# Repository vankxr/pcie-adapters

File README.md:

# pcie-adapters
Collection of PCI Express adapter hardware

## Authors

* **João Silva** - [vankxr](https://github.com/vankxr)

## License

The content of this repository is licensed under the [GNU General Public License v3.0](LICENSE).

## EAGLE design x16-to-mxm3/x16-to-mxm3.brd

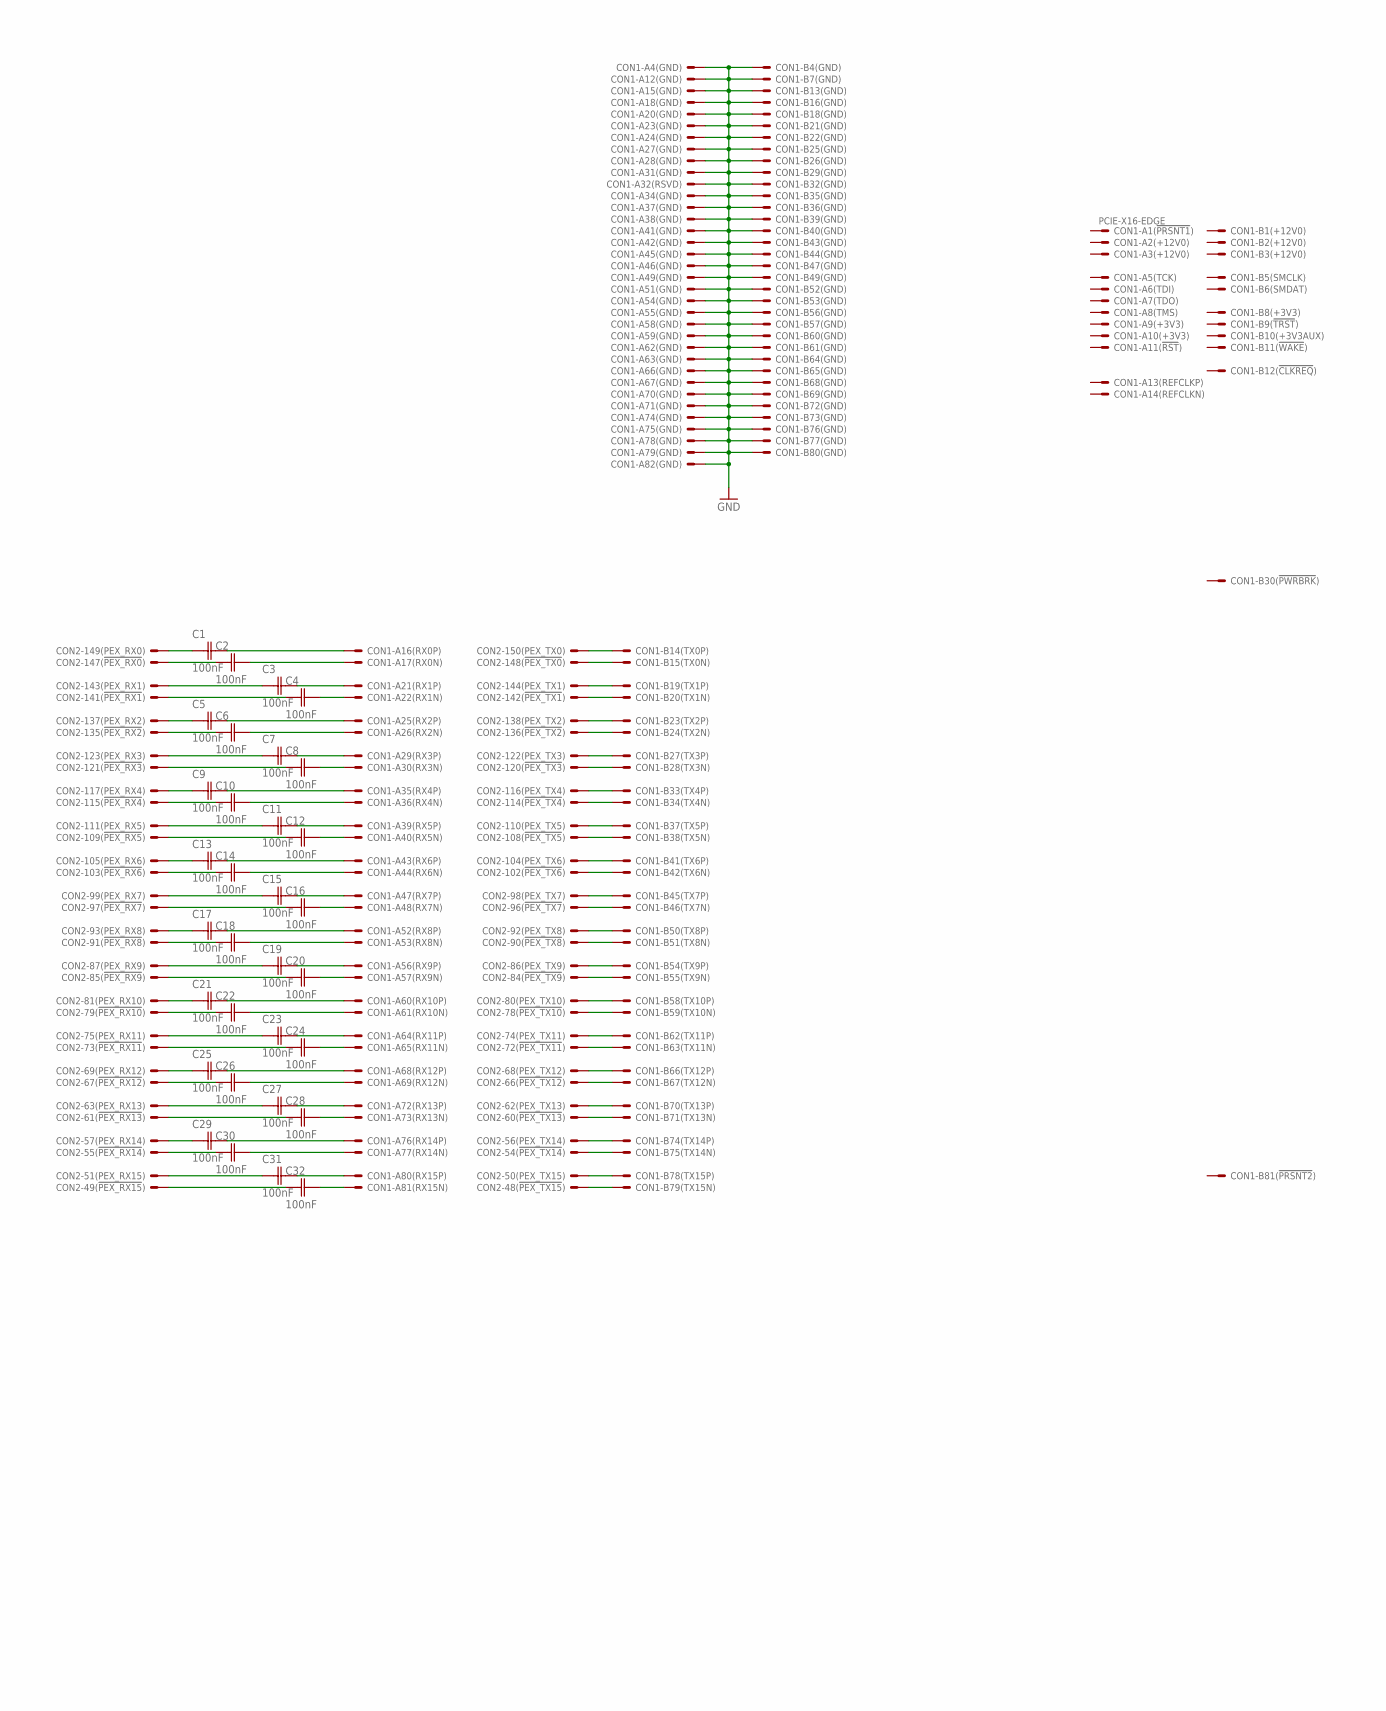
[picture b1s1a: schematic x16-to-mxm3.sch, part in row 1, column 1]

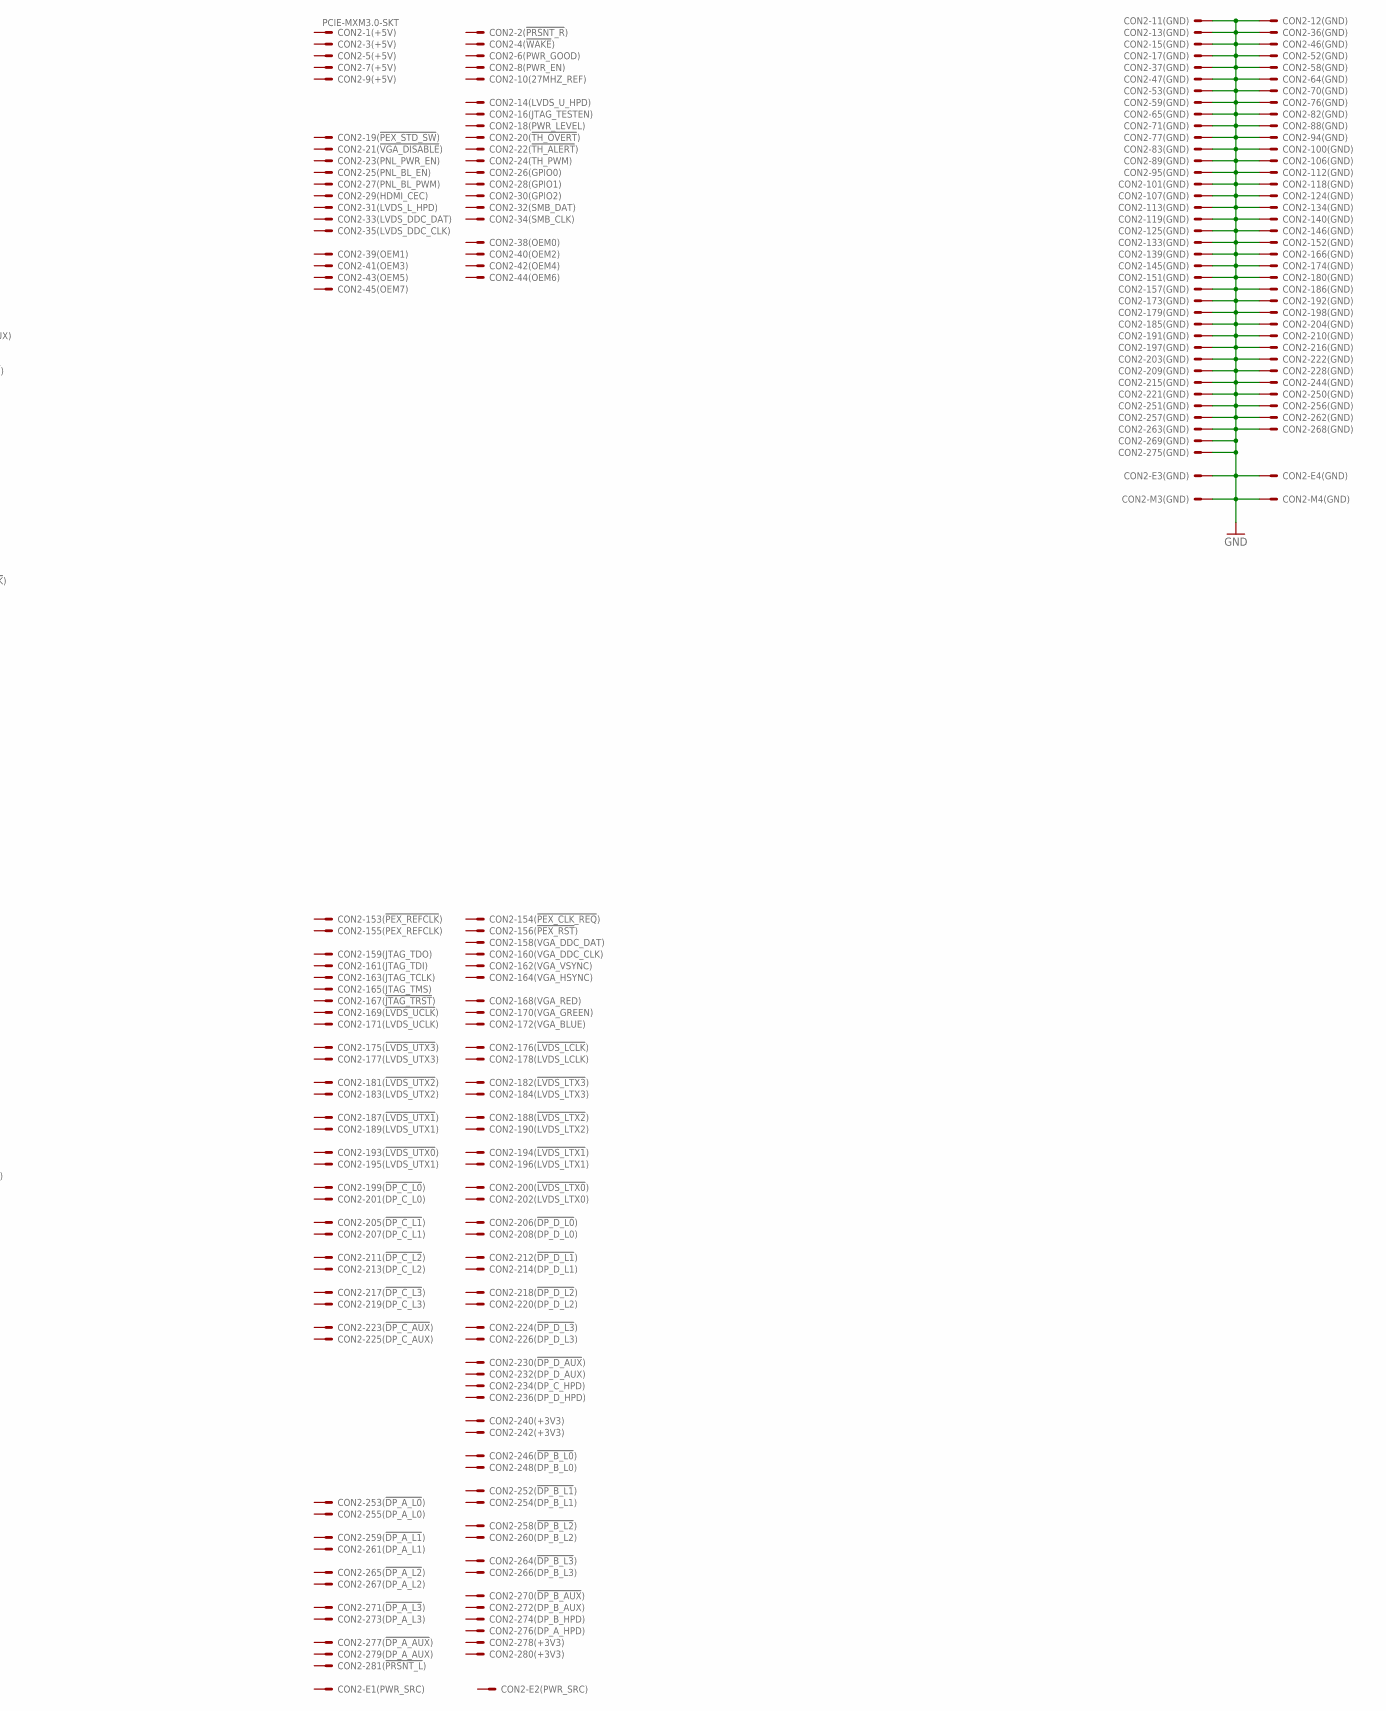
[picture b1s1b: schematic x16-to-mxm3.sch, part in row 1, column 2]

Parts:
C1, C2, C3, C4, C5, C6, C7, C8, C9, C10, C11, C12, C13, C14, C15, C16, C17, C18, C19, C20, C21, C22, C23, C24, C25, C26, C27, C28, C29, C30, C31, C32: 100nF; CAP0402
CON1: PCIE-X16-EDGE
CON2: PCIE-MXM3.0-SKT

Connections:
GND: CON1.A4, CON1.A12, CON1.A15, CON1.A18, CON1.A20, CON1.A23, CON1.A24, CON1.A27, CON1.A28, CON1.A31, CON1.A32, CON1.A34, CON1.A37, CON1.A38, CON1.A41, CON1.A42, CON1.A45, CON1.A46, CON1.A49, CON1.A51, CON1.A54, CON1.A55, CON1.A58, CON1.A59, CON1.A62, CON1.A63, CON1.A66, CON1.A67, CON1.A70, CON1.A71, CON1.A74, CON1.A75, CON1.A78, CON1.A79, CON1.A82, CON1.B4, CON1.B7, CON1.B13, CON1.B16, CON1.B18, CON1.B21, CON1.B22, CON1.B25, CON1.B26, CON1.B29, CON1.B32, CON1.B35, CON1.B36, CON1.B39, CON1.B40, CON1.B43, CON1.B44, CON1.B47, CON1.B49, CON1.B52, CON1.B53, CON1.B56, CON1.B57, CON1.B60, CON1.B61, CON1.B64, CON1.B65, CON1.B68, CON1.B69, CON1.B72, CON1.B73, CON1.B76, CON1.B77, CON1.B80, CON2.11, CON2.12, CON2.13, CON2.15, CON2.17, CON2.36, CON2.37, CON2.46, CON2.47, CON2.52, CON2.53, CON2.58, CON2.59, CON2.64, CON2.65, CON2.70, CON2.71, CON2.76, CON2.77, CON2.82, CON2.83, CON2.88, CON2.89, CON2.94, CON2.95, CON2.100, CON2.101, CON2.106, CON2.107, CON2.112, CON2.113, CON2.118, CON2.119, CON2.124, CON2.125, CON2.133, CON2.134, CON2.139, CON2.140, CON2.145, CON2.146, CON2.151, CON2.152, CON2.157, CON2.166, CON2.173, CON2.174, CON2.179, CON2.180, CON2.185, CON2.186, CON2.191, CON2.192, CON2.197, CON2.198, CON2.203, CON2.204, CON2.209, CON2.210, CON2.215, CON2.216, CON2.221, CON2.222, CON2.228, CON2.244, CON2.250, CON2.251, CON2.256, CON2.257, CON2.262, CON2.263, CON2.268, CON2.269, CON2.275, CON2.E3, CON2.E4, CON2.M3, CON2.M4
unnamed: CON1.B14, CON2.150
unnamed: CON1.B15, CON2.148
unnamed: CON1.B19, CON2.144
unnamed: CON1.B20, CON2.142
unnamed: CON1.B23, CON2.138
unnamed: CON1.B24, CON2.136
unnamed: CON1.B27, CON2.122
unnamed: CON1.B28, CON2.120
unnamed: CON1.B33, CON2.116
unnamed: CON1.B34, CON2.114
unnamed: CON1.B37, CON2.110
unnamed: CON1.B38, CON2.108
unnamed: CON1.B41, CON2.104
unnamed: CON1.B42, CON2.102
unnamed: CON1.B45, CON2.98
unnamed: CON1.B46, CON2.96
unnamed: CON1.B50, CON2.92
unnamed: CON1.B51, CON2.90
unnamed: CON1.B54, CON2.86
unnamed: CON1.B55, CON2.84
unnamed: CON1.B58, CON2.80
unnamed: CON1.B59, CON2.78
unnamed: CON1.B62, CON2.74
unnamed: CON1.B63, CON2.72
unnamed: CON1.B66, CON2.68
unnamed: CON1.B67, CON2.66
unnamed: CON1.B70, CON2.62
unnamed: CON1.B71, CON2.60
unnamed: CON1.B74, CON2.56
unnamed: CON1.B75, CON2.54
unnamed: CON1.B78, CON2.50
unnamed: CON1.B79, CON2.48
unnamed: C4.2 (C2), CON1.A22
unnamed: C8.2 (C2), CON1.A30
unnamed: C12.2 (C2), CON1.A40
unnamed: C16.2 (C2), CON1.A48
unnamed: C20.2 (C2), CON1.A57
unnamed: C24.2 (C2), CON1.A65
unnamed: C28.2 (C2), CON1.A73
unnamed: C32.2 (C2), CON1.A81
unnamed: C2.2 (C2), CON1.A17
unnamed: C6.2 (C2), CON1.A26
unnamed: C10.2 (C2), CON1.A36
unnamed: C14.2 (C2), CON1.A44
unnamed: C18.2 (C2), CON1.A53
unnamed: C22.2 (C2), CON1.A61
unnamed: C26.2 (C2), CON1.A69
unnamed: C30.2 (C2), CON1.A77
unnamed: C1.2 (C2), CON1.A16
unnamed: C5.2 (C2), CON1.A25
unnamed: C9.2 (C2), CON1.A35
unnamed: C13.2 (C2), CON1.A43
unnamed: C17.2 (C2), CON1.A52
unnamed: C21.2 (C2), CON1.A60
unnamed: C25.2 (C2), CON1.A68
unnamed: C29.2 (C2), CON1.A76
unnamed: C3.2 (C2), CON1.A21
unnamed: C7.2 (C2), CON1.A29
unnamed: C11.2 (C2), CON1.A39
unnamed: C15.2 (C2), CON1.A47
unnamed: C19.2 (C2), CON1.A56
unnamed: C23.2 (C2), CON1.A64
unnamed: C27.2 (C2), CON1.A72
unnamed: C31.2 (C2), CON1.A80
unnamed: C29.1 (C1), CON2.57
unnamed: C25.1 (C1), CON2.69
unnamed: C21.1 (C1), CON2.81
unnamed: C17.1 (C1), CON2.93
unnamed: C13.1 (C1), CON2.105
unnamed: C9.1 (C1), CON2.117
unnamed: C5.1 (C1), CON2.137
unnamed: C1.1 (C1), CON2.149
unnamed: C31.1 (C1), CON2.51
unnamed: C27.1 (C1), CON2.63
unnamed: C23.1 (C1), CON2.75
unnamed: C19.1 (C1), CON2.87
unnamed: C15.1 (C1), CON2.99
unnamed: C7.1 (C1), CON2.123
unnamed: C3.1 (C1), CON2.143
unnamed: C30.1 (C1), CON2.55
unnamed: C26.1 (C1), CON2.67
unnamed: C22.1 (C1), CON2.79
unnamed: C18.1 (C1), CON2.91
unnamed: C14.1 (C1), CON2.103
unnamed: C10.1 (C1), CON2.115
unnamed: C6.1 (C1), CON2.135
unnamed: C2.1 (C1), CON2.147
unnamed: C32.1 (C1), CON2.49
unnamed: C28.1 (C1), CON2.61
unnamed: C24.1 (C1), CON2.73
unnamed: C20.1 (C1), CON2.85
unnamed: C16.1 (C1), CON2.97
unnamed: C12.1 (C1), CON2.109
unnamed: C8.1 (C1), CON2.121
unnamed: C4.1 (C1), CON2.141
unnamed: C11.1 (C1), CON2.111

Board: 2 copper layers, 34 parts (0 on the bottom side), 97 nets, no tracks yet.

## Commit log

2022-10-15 Add x16 to MXM3
